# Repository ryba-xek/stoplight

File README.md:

# stoplight
E-bike stop light PCB

Based on a red reflector of a GAZ-2705 van.
Size: 50x120 mm

Forum topic: https://electrotransport.ru/ussr/index.php?topic=56362.msg1452935

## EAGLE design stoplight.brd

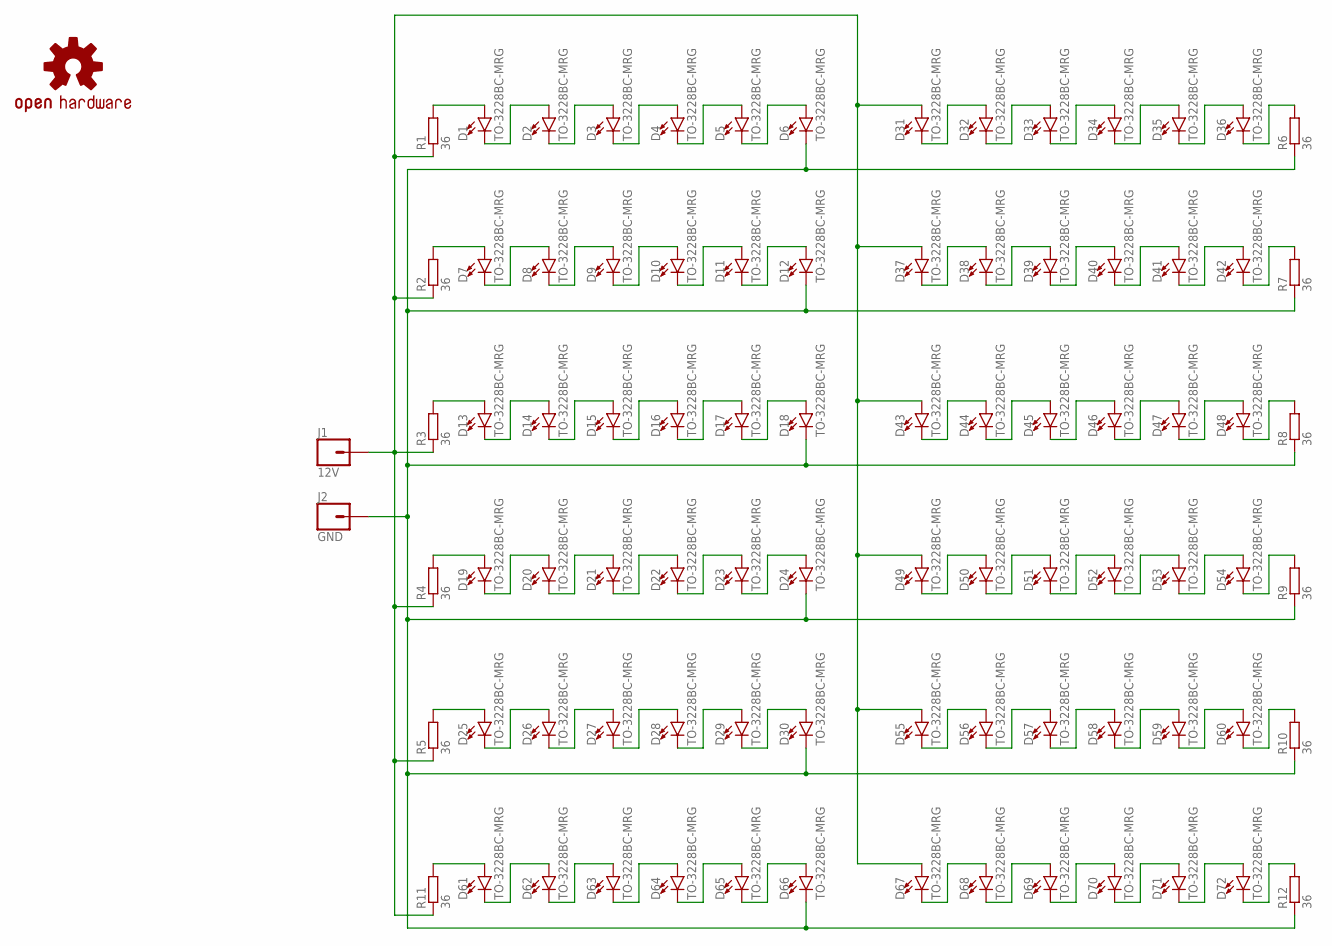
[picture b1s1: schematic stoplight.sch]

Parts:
D1, D2, D3, D4, D5, D6, D7, D8, D9, D10, D11, D12, D13, D14, D15, D16, D17, D18, D19, D20, D21, D22, D23, D24, D25, D26, D27, D28, D29, D30, D31, D32, D33, D34, D35, D36, D37, D38, D39, D40, D41, D42, D43, D44, D45, D46, D47, D48, D49, D50, D51, D52, D53, D54, D55, D56, D57, D58, D59, D60, D61, D62, D63, D64, D65, D66, D67, D68, D69, D70, D71, D72: TO-3228BC-MRG; TO-3228BC
J1: 12V; 1X01_LONGPAD
J2: GND; 1X01_LONGPAD
LOGO1: OSHW-LOGOS-COPPER; OSHW-LOGO-S_COPPER
R1, R2, R3, R4, R5, R6, R7, R8, R9, R10, R11, R12: 36; R0805

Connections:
+12V: D31.A, D37.A, D43.A, D49.A, D55.A, D67.A, J1.1, R1.1, R2.1, R3.1, R4.1, R5.1, R11.1
GND: D6.C, D12.C, D18.C, D24.C, D30.C, D66.C, J2.1, R6.1, R7.1, R8.1, R9.1, R10.1, R12.1
unnamed: D1.A, R1.2
unnamed: D1.C, D2.A
unnamed: D2.C, D3.A
unnamed: D3.C, D4.A
unnamed: D4.C, D5.A
unnamed: D5.C, D6.A
unnamed: D36.C, R6.2
unnamed: D7.A, R2.2
unnamed: D7.C, D8.A
unnamed: D8.C, D9.A
unnamed: D9.C, D10.A
unnamed: D10.C, D11.A
unnamed: D11.C, D12.A
unnamed: D31.C, D32.A
unnamed: D13.A, R3.2
unnamed: D13.C, D14.A
unnamed: D14.C, D15.A
unnamed: D15.C, D16.A
unnamed: D16.C, D17.A
unnamed: D17.C, D18.A
unnamed: D32.C, D33.A
unnamed: D19.A, R4.2
unnamed: D19.C, D20.A
unnamed: D20.C, D21.A
unnamed: D21.C, D22.A
unnamed: D22.C, D23.A
unnamed: D23.C, D24.A
unnamed: D33.C, D34.A
unnamed: D25.A, R5.2
unnamed: D25.C, D26.A
unnamed: D26.C, D27.A
unnamed: D27.C, D28.A
unnamed: D28.C, D29.A
unnamed: D29.C, D30.A
unnamed: D34.C, D35.A
unnamed: D35.C, D36.A
unnamed: D42.C, R7.2
unnamed: D37.C, D38.A
unnamed: D38.C, D39.A
unnamed: D39.C, D40.A
unnamed: D40.C, D41.A
unnamed: D41.C, D42.A
unnamed: D48.C, R8.2
unnamed: D43.C, D44.A
unnamed: D44.C, D45.A
unnamed: D45.C, D46.A
unnamed: D46.C, D47.A
unnamed: D47.C, D48.A
unnamed: D54.C, R9.2
unnamed: D49.C, D50.A
unnamed: D50.C, D51.A
unnamed: D51.C, D52.A
unnamed: D52.C, D53.A
unnamed: D53.C, D54.A
unnamed: D60.C, R10.2
unnamed: D55.C, D56.A
unnamed: D56.C, D57.A
unnamed: D57.C, D58.A
unnamed: D58.C, D59.A
unnamed: D59.C, D60.A
unnamed: D61.A, R11.2
unnamed: D61.C, D62.A
unnamed: D62.C, D63.A
unnamed: D63.C, D64.A
unnamed: D64.C, D65.A
unnamed: D65.C, D66.A
unnamed: D67.C, D68.A
unnamed: D68.C, D69.A
unnamed: D69.C, D70.A
unnamed: D70.C, D71.A
unnamed: D71.C, D72.A
unnamed: D72.C, R12.2

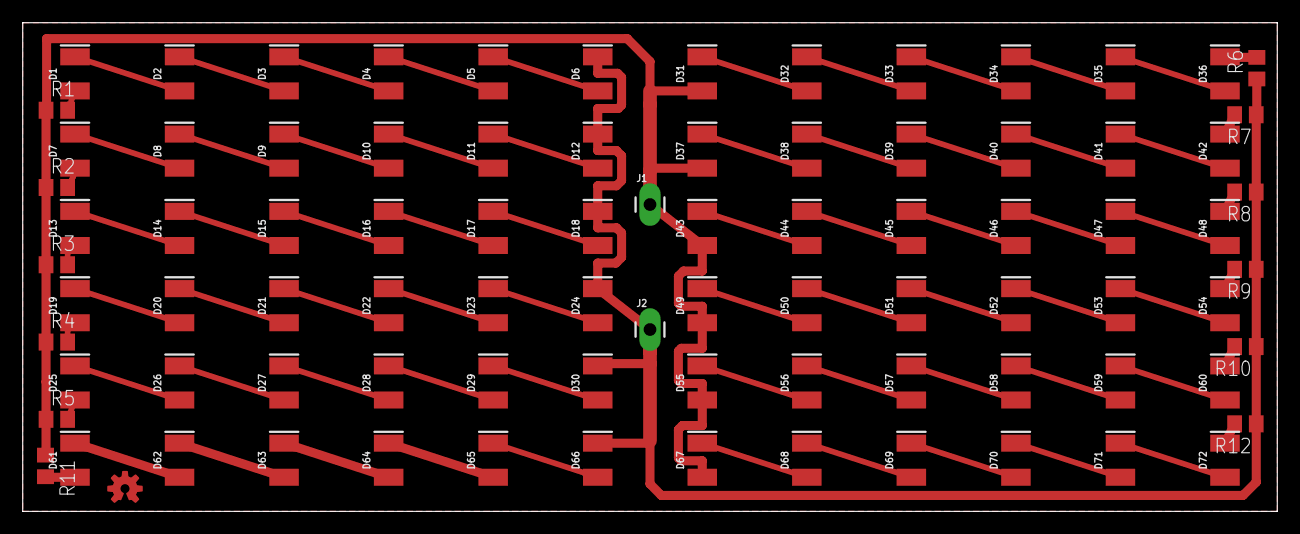
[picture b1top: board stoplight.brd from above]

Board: 2 copper layers, 110.4 x 43.0 mm, 87 parts (0 on the bottom side), 74 nets.

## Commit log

2018-10-01 Version 1
2018-10-01 added a couple photos

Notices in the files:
parts and their libraries:
SparkFun-Connectors: Licensing: Creative Commons ShareAlike 4.0 International - https://creativecommons.org/licenses/by-sa/4.0
